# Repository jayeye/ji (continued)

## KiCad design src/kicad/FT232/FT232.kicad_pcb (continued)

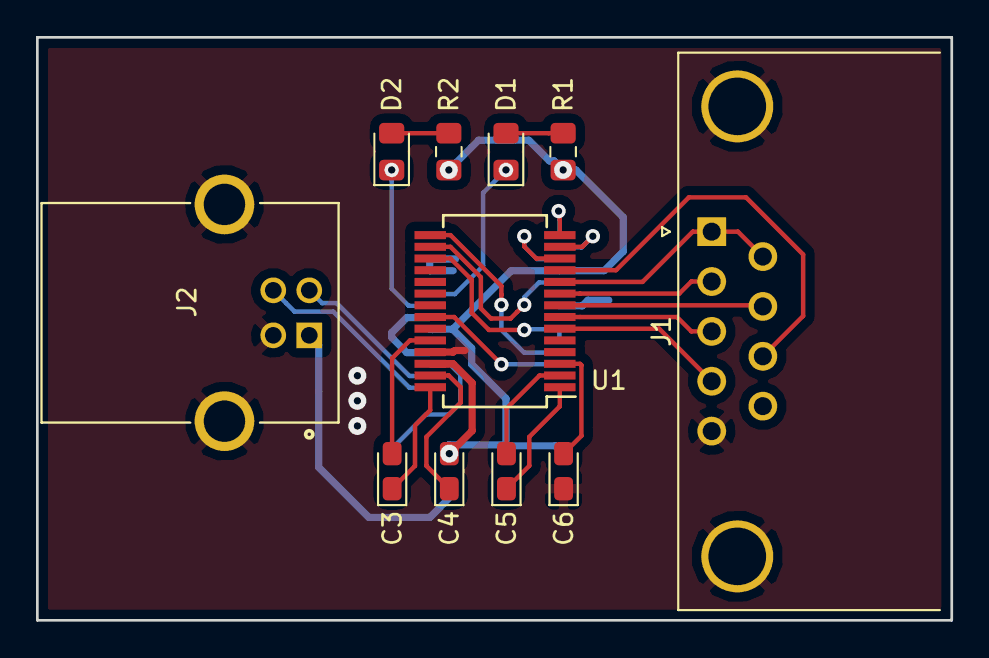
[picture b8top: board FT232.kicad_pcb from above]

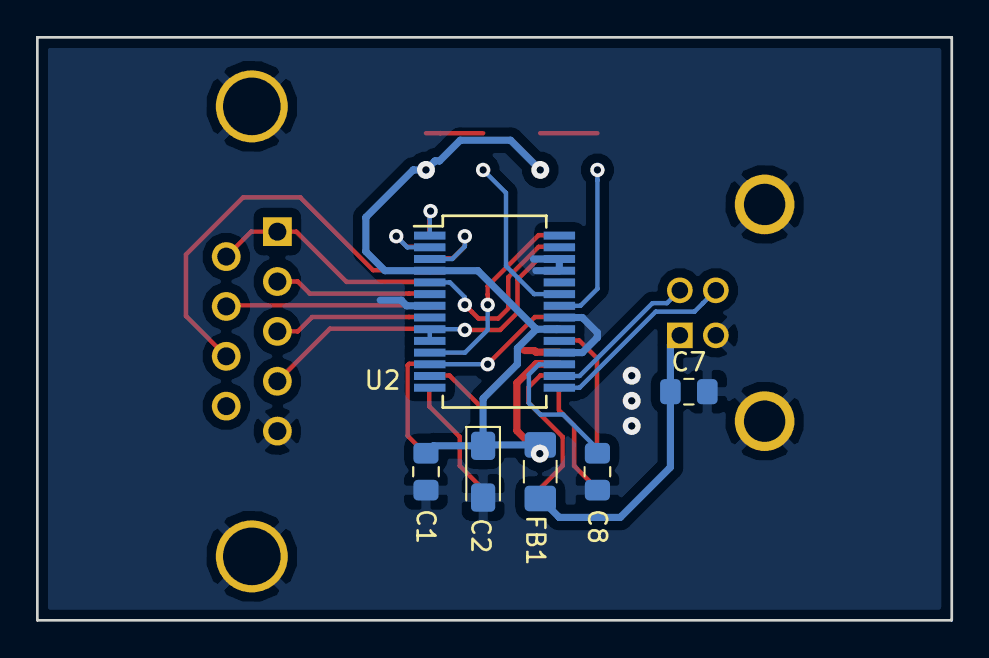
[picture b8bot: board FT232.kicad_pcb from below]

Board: 2 copper layers, 50.8 x 32.4 mm, 17 parts (6 on the bottom side), 29 nets.

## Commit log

2019-03-18 rebuilt
2019-03-18 pngs
2019-03-23 pretty pictures
2019-03-25 fixed g1/g2 inversion, removed virtual diode bypass
2019-03-27 pics
2019-03-27 cleaned up PSU circuitry; added bypass capacitor to EEPROM
2019-03-30 rerouted to expose control signals on optional headers
2019-08-19 La Gioconda
2019-10-24 FT232 import
2019-10-29 kumiko
2019-10-29 more kumiko
2019-10-30 hex kumiko
2019-10-30 hexjpg
2019-11-14 polydreidel
2020-01-29 Adaptor for a KSGER handle to fit in a dremel drill press
2020-09-10 business card front
2020-12-25 Cleaned up and committed the penrose-tiling gift paper
2021-02-25 box drawing characters for emacs
2021-04-08 rosette
2021-10-17 greek words spellable with latin characters
2021-11-19 dhcp6 with prefix delegation
2022-01-04 dice-pics
2022-01-04 latest source
2022-01-12 mail of color
